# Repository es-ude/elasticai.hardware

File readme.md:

# elasticAI.hardware
This repo contains the hardware design files for different generations of the Elastic Node Hardware (ENv). 
This hardware is used for deploying deep learning architectures on embedded hardware and in applications.

## ENv6 - Elastic Node v6
Still in development. See further detailed information in their specific [docu file](v6/readme.md).

## ENv5 - Elastic Node v5
Actual version. See further detailed information in [docu](v5/readme.md).

## ENv4 - Elastic Node v4
Designs are deprecated and not longer used.

## ENv3 - Elastic Node v3
Designs are deprecated and not longer used.

## ENv2 - Elastic Node v2
Designs are deprecated and not longer used.

## ENv1 - Elastic Node v1
Designs are deprecated and not longer used.

## power - Elastic Power Modules
Designs are the actual version. See further detailed information in [docu](power/readme.md).

## measurement - Measurement Equipment for R&S MXO4
This two designs can be used for performing Frequency Response Analysis using the R&S MXO4 oscilloscope in which the Device-Under-Test (DUT) needs an input offset.
State: Active used

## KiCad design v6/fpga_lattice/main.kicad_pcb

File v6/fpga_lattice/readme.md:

# ENv6 FPGA Board: Lattice iCE40UP5K

FPGA board (shield, rev 1.0, 4-layer PCB) for the ENv6 base board. FPGA board ID: **1** (R2 = 1 kΩ to GND on `FPGA_DETECT`, see the [auto-identification](../readme.md#auto-identification-of-connected-boards)).

## Contents

- Lattice iCE40UP5K-SG48 (U1)
- W25Q16JVUX quad-SPI flash (U2), shared with the MCU via the SPI1/QSPI lines of the connector
- Si5351A clock generator (J1) with 25 MHz crystal (Y1): controlled by the MCU via I2C, output enable `FPGA_OSC_EN`; one output drives the FPGA global clock input (`FPGA_SYS_CLK`, test point TP1), a second output is available at test point TP2
- Status LED (D1, R1 = 750 Ω) on an FPGA IO (`IOT_36B`)
- ID resistor R2 (1 kΩ) on `FPGA_DETECT`
- Pull-ups (R3 … R7, 10 kΩ to `VDD`) on the flash lines `WP`, `HOLD`, `CS` and on `FPGA_PR_~{RST}`, `FPGA_PR_DONE`

## Power Supply

| Rail   | Pins      | Net    | Use                                                  |
|--------|-----------|--------|------------------------------------------------------|
| `PSU1` | C3 … C8   | `+1V2` | iCE40 core (`VCC`) and PLL (`VCCPLL`)                |
| `PSU4` | C19 … C24 | `VDD`  | I/O banks, `VPP_2V5`, flash, Si5351A, pull-ups       |

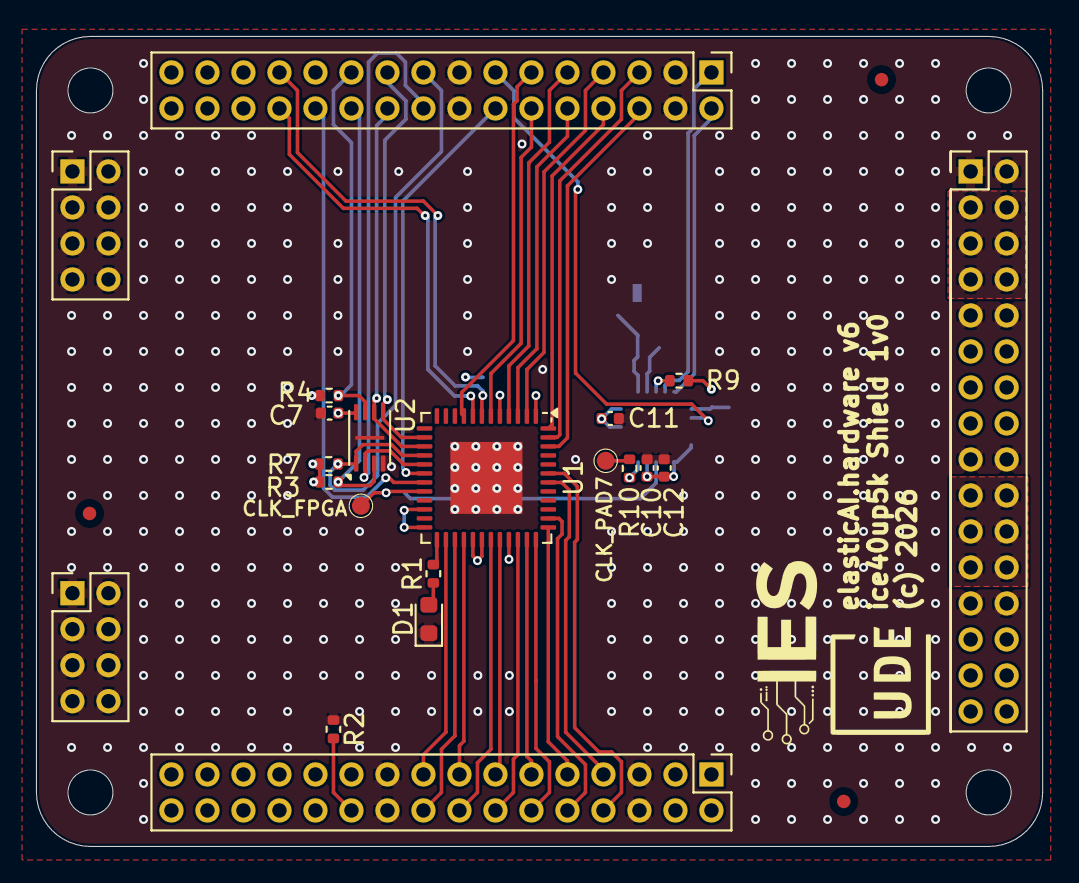
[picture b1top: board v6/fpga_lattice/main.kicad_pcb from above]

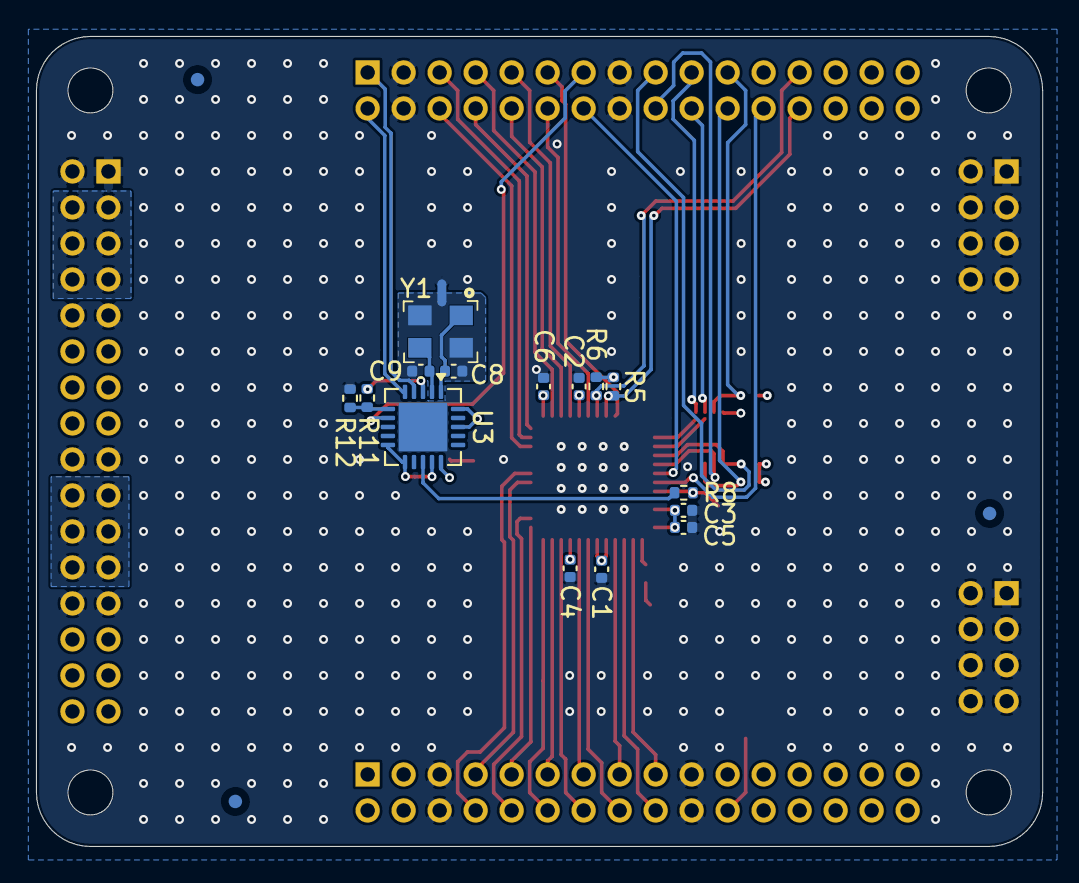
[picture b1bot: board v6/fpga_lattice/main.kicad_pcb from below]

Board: 4 copper layers, 55.9 x 45.0 mm, 39 parts (19 on the bottom side), 48 nets.

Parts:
B1: ExtensionBoard_ENv6
C1, C2, C3, C4, C5, C6, C7, C10, C11, C12: 1u; C_0402_1005Metric
C8, C9: 12p; C_0402_1005Metric
D1: LED_0603; LED_0603_1608Metric
FID1, FID2, FID3, FID4, FID5, FID6: Fiducial; Fiducial_0.75mm_Mask1.5mm
NT1: NetTie_2; NetTie-2_SMD_Pad0.5mm
R1: 750R; R_0402_1005Metric
R2: 1k; R_0402_1005Metric
R3, R4, R5, R6, R7: 10k; R_0402_1005Metric
R8, R9, R10, R11, R12: 27R; R_0402_1005Metric
TP1: CLK_FPGA; TestPoint_Pad_D1.0mm
TP2: CLK_PAD7; TestPoint_Pad_D1.0mm
U1: ICE40UP5K-SG48ITR50; QFN-48-1EP_7x7mm_P0.5mm_EP5.15x5.15mm
U2: W25Q16JVUX; USON-8-1EP_3x2mm_P0.5mm_EP0.2x1.6mm
U3: Si5351A-B-GM; QFN-20-1EP_4x4mm_P0.5mm_EP2.7x2.7mm
Y1: KX7-25M; KX-7

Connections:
+1V2: B1.C3, B1.C4, B1.C5, B1.C6, B1.C7, B1.C8, C1.2, C2.2, U1.5 (VCC), U1.29 (VCCPLL), U1.30 (VCC)
/FLASH_~CS: B1.A17, R7.2, U1.16 (IOB_35B_SPI_SS), U2.1 (~CS)
/FPGA_FLASH_SI: B1.A19, U1.14 (IOB_32A_SPI_SO), U2.5 (SI/IO0)
/FPGA_FLASH_SK: B1.A20, U1.15 (IOB_34A_SPI_SCK), U2.6 (SCK)
/FPGA_FLASH_SO: B1.A18, U1.17 (IOB_33B_SPI_SI), U2.2 (SO/IO1)
/FPGA_FLASH_~HD: B1.A21, R4.2, U2.7 (~HOLD/IO3)
/FPGA_FLASH_~WP: B1.A22, R3.2, U2.3 (~WP/IO2)
/FPGA_IO_0: B1.A5, U1.47 (IOB_2A)
/FPGA_IO_1: B1.A6, U1.46 (IOB_0A)
/FPGA_IO_2: B1.A7, U1.2 (IOB_6A)
/FPGA_IO_3: B1.A8, U1.48 (IOB_4A)
/FPGA_IO_4: B1.A9, U1.4 (IOB_8A)
/FPGA_IO_5: B1.A10, U1.3 (IOB_9B)
/FPGA_IO_6: B1.A11, U1.9 (IOB_16A)
/FPGA_IO_7: B1.A12, U1.6 (IOB_13B)
/FPGA_IO_A_0: B1.B18, U1.27 (IOT_38B)
/FPGA_IO_A_1: B1.B17, U1.26 (IOT_39A)
/FPGA_IO_A_2: B1.B16, U1.31 (IOT_42B)
/FPGA_IO_A_3: B1.B15, U1.28 (IOT_41A)
/FPGA_IO_A_4: B1.B14, U1.34 (IOT_44B)
/FPGA_IO_A_5: B1.B13, U1.32 (IOT_43A)
/FPGA_IO_A_6: B1.B12, U1.36 (IOT_48B)
/FPGA_IO_A_7: B1.B11, U1.35 (IOT_46B_G0)
/FPGA_IO_A_8: B1.B10, U1.38 (IOT_50B)
/FPGA_IO_A_9: B1.B9, U1.37 (IOT_45A_G1)
/FPGA_IO_A_10: B1.B8, U1.43 (IOT_49A)
/FPGA_IO_A_11: B1.B7, U1.42 (IOT_51A)
/FPGA_OSC_EN: B1.A13, U3.7 (OEB)
/FPGA_PR_DONE: B1.A25, R6.2, U1.7 (CDONE)
/FPGA_PR_~RST: B1.A26, R5.2, U1.8 (~CRESET_B)
/FPGA_SYS_CLK: R8.2, TP1.1 (1_1), U1.20 (IOB_25B_G3)
/FPGA_USR_~RST: B1.A24, U1.19 (IOB_29B)
/FPGA_~CS: B1.A14, U1.18 (IOB_31B)
/GND_QRZ: C8.2, C9.2, NT1.2, Y1.2 (SH), Y1.4 (SH)
/I2C_SCL: B1.A1, U3.4 (SCL)
/I2C_SDA: B1.A2, U3.5 (SDA)
GND: B1.A3, B1.A4, B1.A15, B1.A16, B1.B5, B1.B6, B1.B19, B1.B20, B1.C1, B1.C2, B1.C9, B1.C10, B1.C17, B1.C18, B1.C25, B1.C26, B1.D1, B1.D2, B1.D3, B1.D4, B1.D5, B1.D6, B1.D7, B1.D8, B1.E1, B1.E2, B1.E3, B1.E4, B1.E5, B1.E6, B1.E7, B1.E8, C1.1, C2.1, C3.2, C4.2, C5.2, C6.2, C7.2, C10.2, C11.2, C12.2, D1.1 (K), NT1.1, R2.1, R12.2, U1.49 (GND), U2.4 (VSS), U2.9 (VSS), U3.21 (GND)
unnamed: B1.B22, R2.2
unnamed: D1.2 (A), R1.1
unnamed: R10.2, TP2.1 (1_1)
unnamed: R1.2, U1.25 (IOT_36B)
unnamed: R9.1, U3.3 (A0)
unnamed: R8.1, U3.13 (CLK0)
unnamed: R10.1, U3.15 (CLK7)
unnamed: R11.1, R12.1, U3.6 (SSEN)
unnamed: C8.1, U3.1 (XA), Y1.1
unnamed: C9.1, U3.2 (XB), Y1.3
VDD: B1.C19, B1.C20, B1.C21, B1.C22, B1.C23, B1.C24, C3.1, C4.1, C5.1, C6.1, C7.1, C10.1, C11.1, C12.1, R3.1, R4.1, R5.1, R6.1, R7.1, R9.2, R11.2, U1.1 (VCCIO_2), U1.22 (SPI_VCCIO_1), U1.24 (VPP_2V5), U1.33 (VCCIO_0), U2.8 (VCC), U3.10 (VDDOB), U3.11 (VDDOA), U3.14 (VDDOD), U3.18 (VDDOC), U3.20 (VDD)

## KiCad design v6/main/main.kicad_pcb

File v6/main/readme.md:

# ENv6 Base Board

Base board of the ENv6 stack. It carries the MCU, wireless, USB, power management and current sensing, and provides the connector to the swappable FPGA board and the optional application board (see the [top-level readme](../readme.md) for the connector description and the auto-identification scheme).

## Contents

| Block (KiCad sheet)                   | Main parts                                                                                                                                                                                                                                                                                                                                      |
|---------------------------------------|-------------------------------------------------------------------------------------------------------------------------------------------------------------------------------------------------------------------------------------------------------------------------------------------------------------------------------------------------|
| MCU (`MCU.kicad_sch`)                 | RP2354B (U402), 12 MHz crystal, W25Q16 QSPI flash (U401, optional with internal-flash variant), Raspberry Pi radio module (U403) for WLAN, WS2812B status LED (D401), BOOTSEL / RESET / one user button, SWD debug connector (J401), 1×4 header for an external FPGA JTAG probe (J402), board detection (two 10 kΩ pull-ups R401/R402 + 1 µF)   |
| Power (`Power.kicad_sch`)             | USB-C (J302), Li-ion battery connector (J_BATT301), BQ25188 charger (U301), LP873300 programmable multi-output supply (IC301, four rails PSU1 … PSU4), TLV73333 3.3 V LDO (U302)                                                                                                                                                                |
| Peripherals (`Peripherals.kicad_sch`) | PAC1954 4-channel current/power monitor (U201, 1 Ω shunts), microSD slot (J201, SPI0), 2×2 headers to route the four supply rails through an external Nordic PPK2                                                                                                                                                                               |
| Connector (`connector.kicad_sch`)     | ENv6 base-board connector (MCU/FPGA header, application header, power header, GND headers)                                                                                                                                                                                                                                                      |

## Interfaces

Pin numbers refer to the connector `B401`; the complete pin tables are in the [top-level readme](../readme.md#connector-of-the-base-board).

| Interface                                            | MCU pins                                                           | Connector pins                    |
|------------------------------------------------------|--------------------------------------------------------------------|-----------------------------------|
| I2C0 (also PAC1954)                                  | GP0 (SDA), GP1 (SCL)                                               | A2, A1                            |
| SPI1 to the FPGA board                               | GP12 (RX), GP13 (CS), GP14 (SCK), GP15 (TX)                        | A18, A17, A20, A19                |
| Quad-SPI data lines                                  | GP16 (IO2), GP17 (IO3)                                             | A22, A21                          |
| JTAG                                                 | GP26 (TCK), GP27 (TDO), GP28 (TDI), GP30 (TMS)                     | A30, A29, A32, A31                |
| Configuration lines `FPGA_CFG_1 … 4`                 | GP19 … GP22                                                        | A26, A25, A28, A27                |
| `MCU-FPGA_CS`, `MCU-FPGA_EN_OSC`, `MCU-FPGA_USR-RST` | GP10, GP11, GP18                                                   | A14, A13, A24                     |
| Unused GPIOs                                         | GP2 … GP9                                                          | A6, A5, A8, A7, A10, A9, A12, A11 |
| Application GPIOs / ADC                              | GP33 … GP35, GP40 … GP45 (ADC0 … ADC5)                             | B31 … B29, B28 … B23              |
| Board detection (ADC)                                | GP46 (`FPGA_DETECT`), GP47 (`APP_DETECT`)                          | B22, B21                          |
| microSD                                              | SPI0: GP36 (RX), GP37 (CS), GP38 (SCK), GP39 (TX)                  | –                                 |
| Radio module                                         | GP23 (`WL_EN`), GP24 (`WL_DATA`), GP25 (`WL_CS`), GP29 (`WL_SCLK`) | –                                 |
| Status LED / button                                  | GP31 (WS2812B), GP32 (user button)                                 | –                                 |

Supply: `VDD_MCU` (3.3 V from the TLV73333) feeds the MCU, `AVDD_ADC` and the detection pull-ups (R401, R402); it is also available on A23 and B32. `VSYS` is on B1 … B4, the four programmable rails `PSU1 … PSU4` on C3 … C32.

BOM: [iBOM](bom/ibom.html)

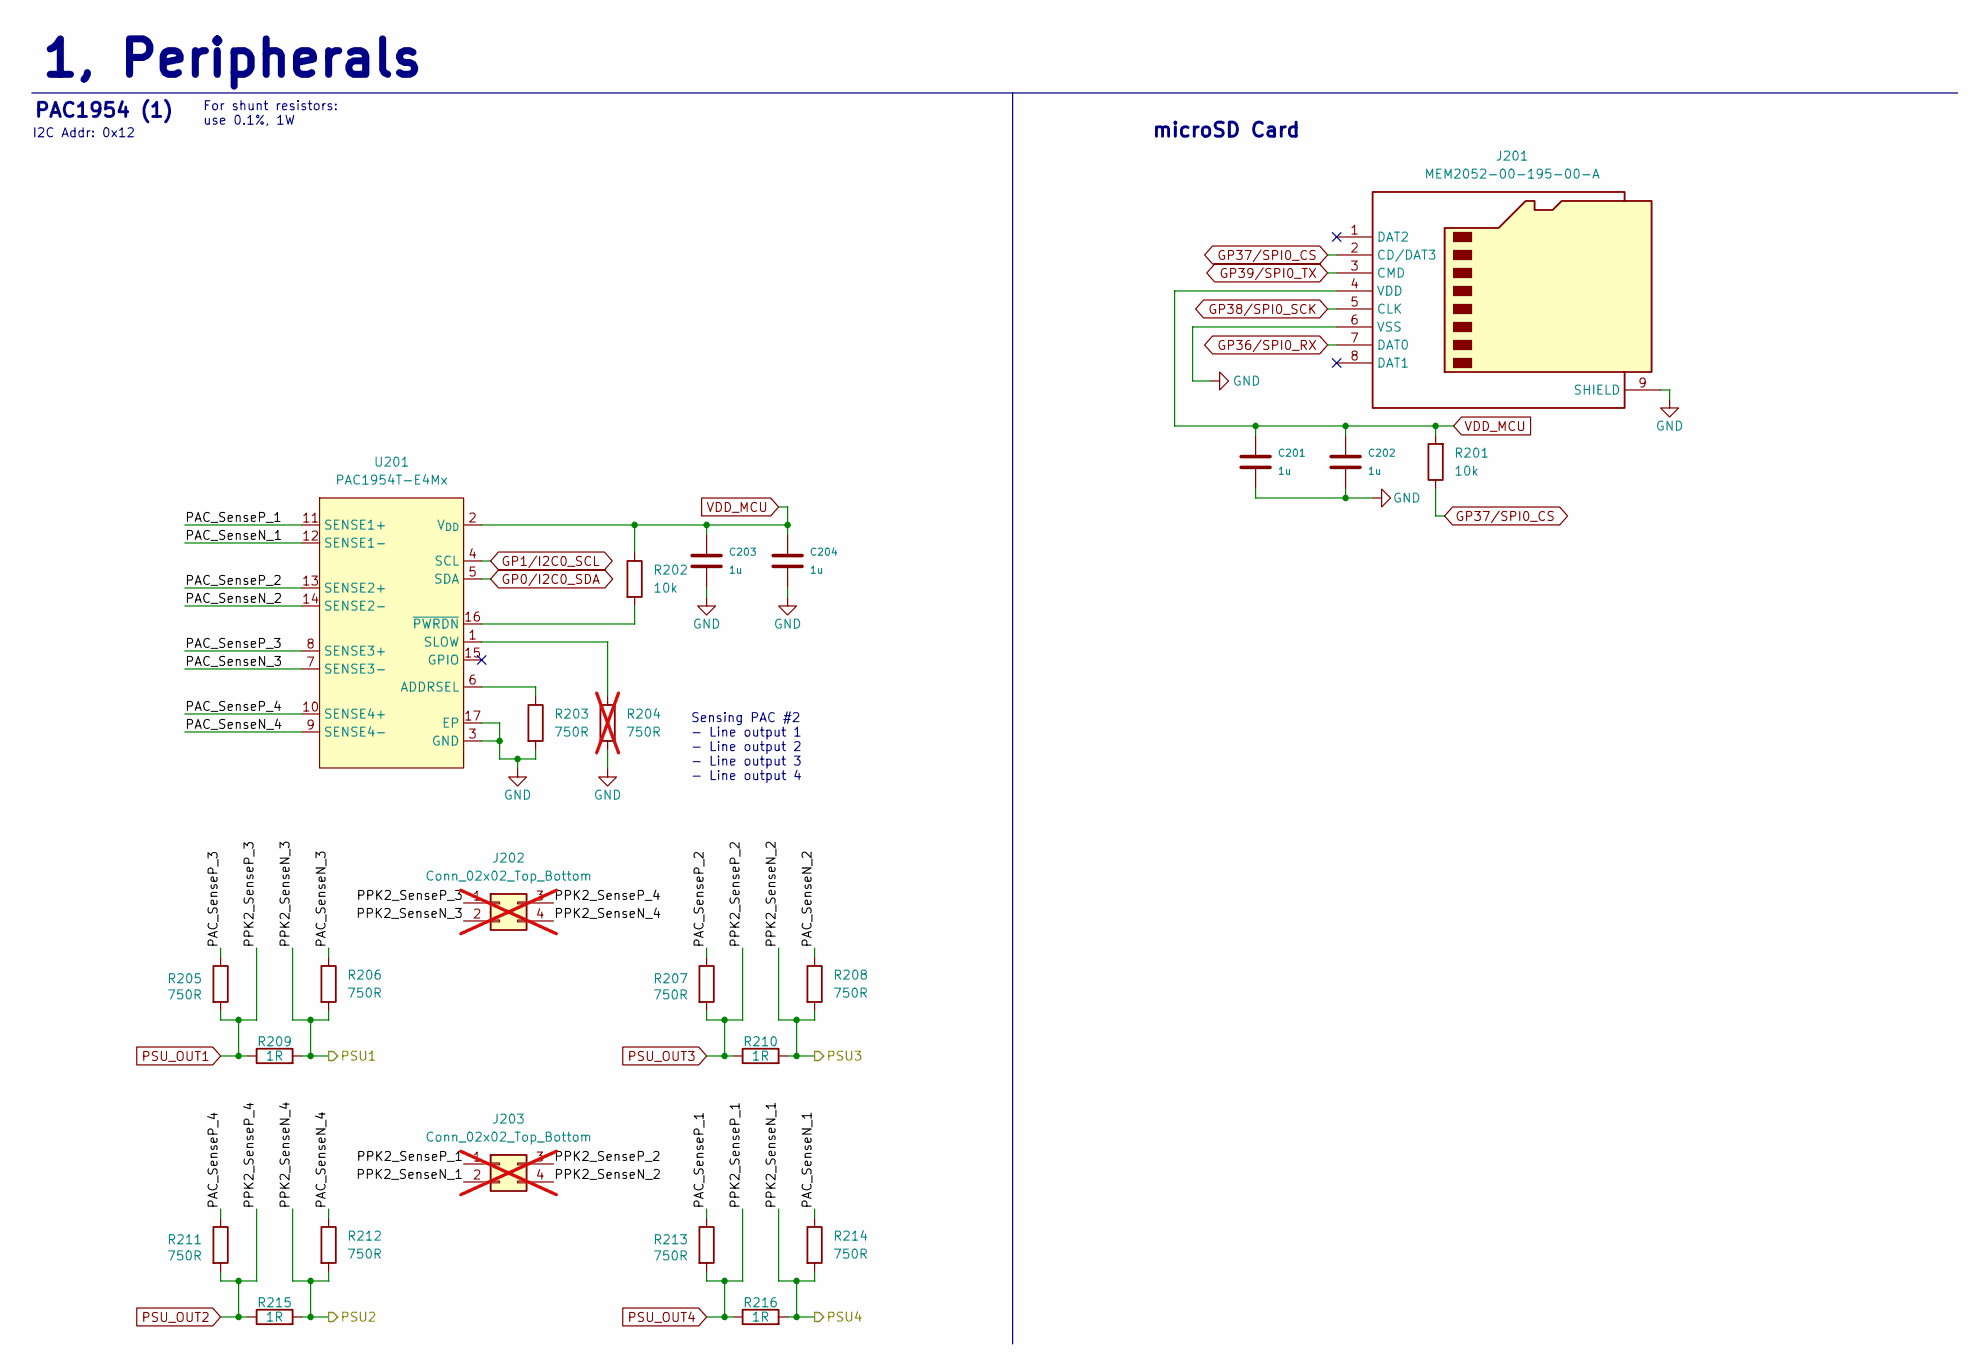
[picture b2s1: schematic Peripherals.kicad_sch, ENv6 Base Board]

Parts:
C201, C202, C203, C204: 1u; C_0402_1005Metric
J201: MEM2052-00-195-00-A; MEM20520019500A; Mouser Part Number 640-MEM20520019500A
J202, J203: Conn_02x02_Top_Bottom; PinHeader_2x02_P2.00mm_Vertical; not fitted
R201, R202: 10k; R_0402_1005Metric
R203, R205, R206, R207, R208, R211, R212, R213, R214: 750R; R_0402_1005Metric
R204: 750R; R_0402_1005Metric; not fitted
R209, R210, R215, R216: 1R; R_0603_1608Metric
U201: PAC1954T-E4Mx; VQFN-16-1EP_3x3mm_P0.5mm_EP1.1x1.1mm

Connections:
/Peripherals/PAC_SenseN_1: R214.1, U201.12 (SENSE1-)
/Peripherals/PAC_SenseN_2: R208.1, U201.14 (SENSE2-)
/Peripherals/PAC_SenseN_3: R206.1, U201.7 (SENSE3-)
/Peripherals/PAC_SenseN_4: R212.1, U201.9 (SENSE4-)
/Peripherals/PAC_SenseP_1: R213.1, U201.11 (SENSE1+)
/Peripherals/PAC_SenseP_2: R207.1, U201.13 (SENSE2+)
/Peripherals/PAC_SenseP_3: R205.1, U201.8 (SENSE3+)
/Peripherals/PAC_SenseP_4: R211.1, U201.10 (SENSE4+)
/V1: J202.2, R206.2, R209.2; also elsewhere on the board
/V2: J202.4, R212.2, R215.2; also elsewhere on the board
/V3: J203.4, R208.2, R210.2; also elsewhere on the board
/V4: J203.2, R214.2, R216.2; also elsewhere on the board
GND: C201.1, C202.1, C203.1, C204.1, J201.6 (VSS), J201.9 (SHIELD), J201.G1 (GND_1), J201.G2 (GND_2), J201.G3 (GND_3), J201.G4 (GND_4), R203.2, R204.2, U201.3 (GND), U201.17 (EP); also elsewhere on the board
GP0/I2C0_SDA: U201.5 (SDA); also elsewhere on the board
GP1/I2C0_SCL: U201.4 (SCL); also elsewhere on the board
GP36/SPI0_RX: J201.7 (DAT0); also elsewhere on the board
GP37/SPI0_CS: J201.2 (CD/DAT3), R201.1; also elsewhere on the board
GP38/SPI0_SCK: J201.5 (CLK); also elsewhere on the board
GP39/SPI0_TX: J201.3 (CMD); also elsewhere on the board
unnamed: R203.1, U201.6 (ADDRSEL)
unnamed: R204.1, U201.1 (SLOW)
unnamed: R202.2, U201.16 (~PWRDN)
PSU_OUT1: J202.1, R205.2, R209.1; also elsewhere on the board
PSU_OUT2: J202.3, R211.2, R215.1; also elsewhere on the board
PSU_OUT3: J203.3, R207.2, R210.1; also elsewhere on the board
PSU_OUT4: J203.1, R213.2, R216.1; also elsewhere on the board
VDD_MCU: C201.2, C202.2, C203.2, C204.2, J201.4 (VDD), R201.2, R202.1, U201.2 (V_{DD}); also elsewhere on the board

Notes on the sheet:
1, Peripherals
PAC1954 (1)
microSD Card
For shunt resistors: use 0.1%, 1W
I2C Addr: 0x12
Sensing PAC #2 - Line output 1 - Line output 2 - Line output 3 - Line output 4

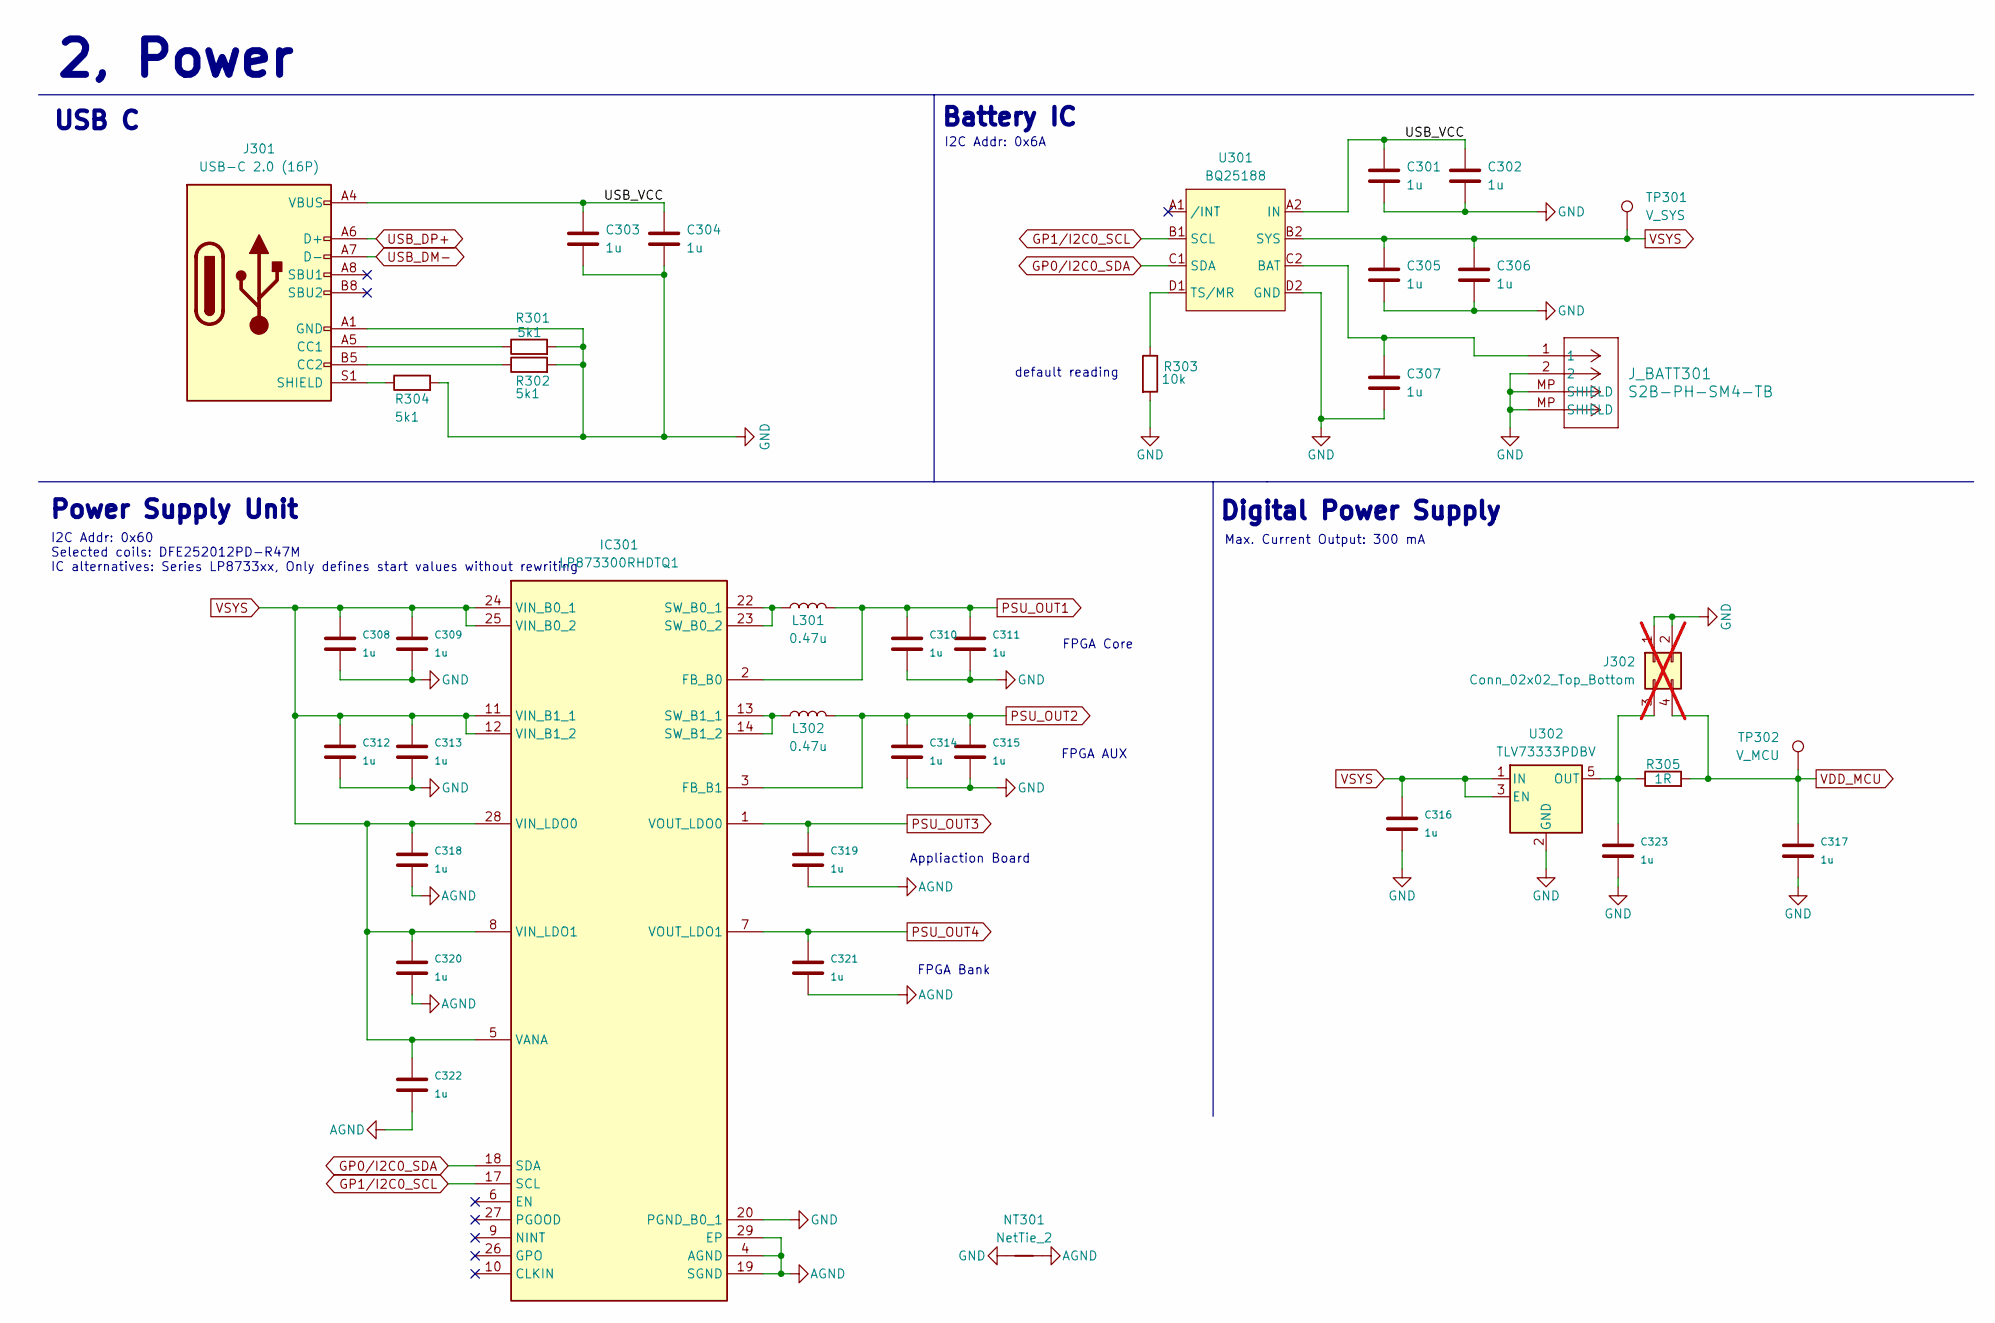
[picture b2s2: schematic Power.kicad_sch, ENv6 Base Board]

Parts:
C301, C302, C303, C304, C305, C306, C307, C308, C309, C310, C311, C312, C313, C314, C315, C316, C317, C318, C319, C320, C321, C322, C323: 1u; C_0402_1005Metric
IC301: LP873300RHDTQ1; QFN50P500X500X100-29N-D; Mouser Part Number 595-LP873300RHDTQ1
J301: USB-C 2.0 (16P); USB_C_Receptacle_16P; MPN 629722000214
J302: Conn_02x02_Top_Bottom; PinHeader_2x02_P2.00mm_Vertical; not fitted
J_BATT301: S2B-PH-SM4-TB; JST_PH_S2B-PH-SM4-TB_1x02-1MP_P2.00mm_Horizontal
L301, L302: 0.47u; L_1008_2520Metric
NT301: NetTie_2; NetTie-2_SMD_Pad0.5mm
R301, R302, R304: 5k1; R_0402_1005Metric
R303: 10k; R_0402_1005Metric
R305: 1R; R_0603_1608Metric
TP301: V_SYS; TestPoint_Pad_D1.0mm
TP302: V_MCU; TestPoint_Pad_D1.0mm
U301: BQ25188; Texas_DSBGA-8_0.9x1.9mm_Layout2x4_P0.5mm
U302: TLV73333PDBV; SOT-23-5

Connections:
/Power/USB_VCC: C301.1, C302.1, C303.1, C304.1, J301.A4 (VBUS), J301.A9 (VBUS), J301.B4 (VBUS), J301.B9 (VBUS), U301.A2 (IN)
AGND: C318.1, C319.1, C320.1, C321.1, C322.1, IC301.4 (AGND), IC301.19 (SGND), IC301.29 (EP), NT301.2
GND: C301.2, C302.2, C303.2, C304.2, C305.2, C306.2, C307.2, C308.1, C309.1, C310.1, C311.1, C312.1, C313.1, C314.1, C315.1, C316.1, C317.1, C323.1, IC301.15 (PGND_B1_1), IC301.16 (PGND_B1_2), IC301.20 (PGND_B0_1), IC301.21 (PGND_B0_2), J301.A1 (GND), J301.A12 (GND), J301.B1 (GND), J301.B12 (GND), J302.1, J302.2, J_BATT301.2, J_BATT301.MP (SHIELD), NT301.1, R301.2, R302.2, R303.2, R304.2, U301.D2 (GND), U302.2 (GND); also elsewhere on the board
GP0/I2C0_SDA: IC301.18 (SDA), U301.C1 (SDA); also elsewhere on the board
GP1/I2C0_SCL: IC301.17 (SCL), U301.B1 (SCL); also elsewhere on the board
unnamed: IC301.22 (SW_B0_1), IC301.23 (SW_B0_2), L301.1
unnamed: IC301.13 (SW_B1_1), IC301.14 (SW_B1_2), L302.1
unnamed: J301.A5 (CC1), R301.1
unnamed: J301.B5 (CC2), R302.1
unnamed: J301.S1 (SHIELD), R304.1
unnamed: C323.2, J302.3, R305.1, U302.5 (OUT)
unnamed: C307.1, J_BATT301.1, U301.C2 (BAT)
unnamed: R303.1, U301.D1 (TS/MR)
PSU_OUT1: C310.2, C311.2, IC301.2 (FB_B0), L301.2; also elsewhere on the board
PSU_OUT2: C314.2, C315.2, IC301.3 (FB_B1), L302.2; also elsewhere on the board
PSU_OUT3: C319.2, IC301.1 (VOUT_LDO0); also elsewhere on the board
PSU_OUT4: C321.2, IC301.7 (VOUT_LDO1); also elsewhere on the board
USB_DM-: J301.A7 (D-), J301.B7 (D-); also elsewhere on the board
USB_DP+: J301.A6 (D+), J301.B6 (D+); also elsewhere on the board
VDD_MCU: C317.2, J302.4, R305.2, TP302.1 (1_1); also elsewhere on the board
VSYS: C305.1, C306.1, C308.2, C309.2, C312.2, C313.2, C316.2, C318.2, C320.2, C322.2, IC301.5 (VANA), IC301.8 (VIN_LDO1), IC301.11 (VIN_B1_1), IC301.12 (VIN_B1_2), IC301.24 (VIN_B0_1), IC301.25 (VIN_B0_2), IC301.28 (VIN_LDO0), TP301.1 (1_1), U301.B2 (SYS), U302.1 (IN), U302.3 (EN); also elsewhere on the board

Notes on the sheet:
Battery IC
FPGA Bank
I2C Addr: 0x6A
default reading
Max. Current Output: 300 mA
USB C
2, Power
FPGA Core
Power Supply Unit
FPGA AUX
I2C Addr: 0x60 Selected coils: DFE252012PD-R47M IC alternatives: Series LP8733xx, Only defines start values without rewriting
Digital Power Supply
Appliaction Board

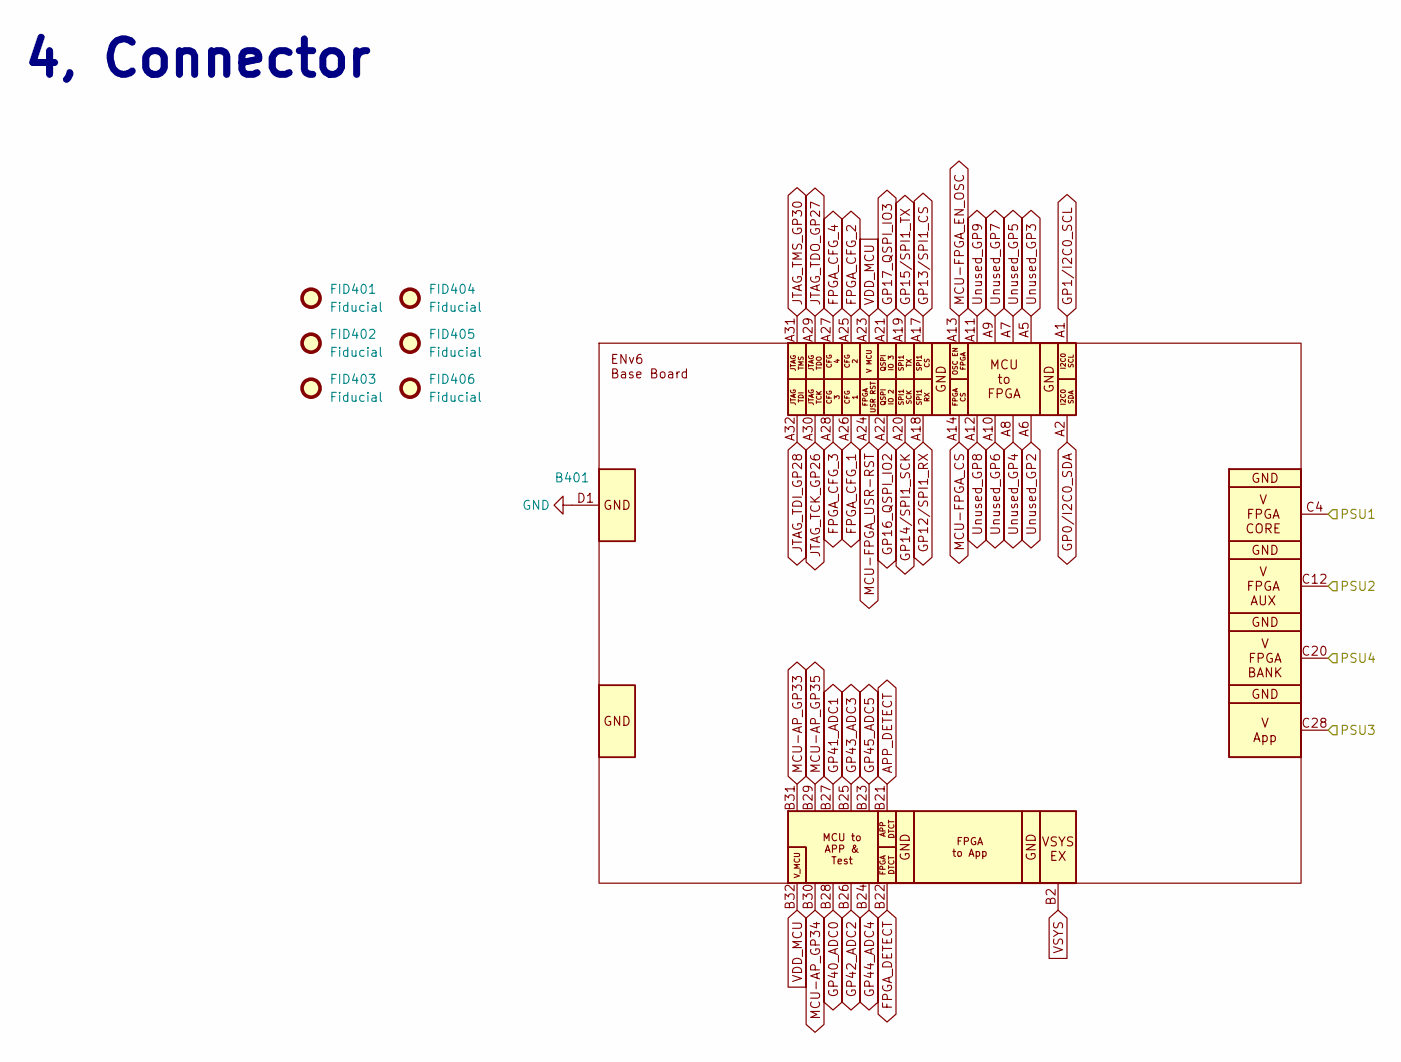
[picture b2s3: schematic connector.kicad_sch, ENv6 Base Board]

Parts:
B401: BaseBoard_ENv6
FID401, FID402, FID403, FID404, FID405, FID406: Fiducial; Fiducial_0.75mm_Mask1.5mm

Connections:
/V1: B401.C3, B401.C4, B401.C5, B401.C6, B401.C7, B401.C8; also elsewhere on the board
/V2: B401.C11, B401.C12, B401.C13, B401.C14, B401.C15, B401.C16; also elsewhere on the board
/V3: B401.C27, B401.C28, B401.C29, B401.C30, B401.C31, B401.C32; also elsewhere on the board
/V4: B401.C19, B401.C20, B401.C21, B401.C22, B401.C23, B401.C24; also elsewhere on the board
APP_DETECT: B401.B21; also elsewhere on the board
FPGA_CFG_1: B401.A26; also elsewhere on the board
FPGA_CFG_2: B401.A25; also elsewhere on the board
FPGA_CFG_3: B401.A28; also elsewhere on the board
FPGA_CFG_4: B401.A27; also elsewhere on the board
FPGA_DETECT: B401.B22; also elsewhere on the board
GND: B401.A3, B401.A4, B401.A15, B401.A16, B401.B5, B401.B6, B401.B19, B401.B20, B401.C1, B401.C2, B401.C9, B401.C10, B401.C17, B401.C18, B401.C25, B401.C26, B401.D1, B401.D2, B401.D3, B401.D4, B401.D5, B401.D6, B401.D7, B401.D8, B401.E1, B401.E2, B401.E3, B401.E4, B401.E5, B401.E6, B401.E7, B401.E8; also elsewhere on the board
GP0/I2C0_SDA: B401.A2; also elsewhere on the board
GP1/I2C0_SCL: B401.A1; also elsewhere on the board
GP12/SPI1_RX: B401.A18; also elsewhere on the board
GP13/SPI1_CS: B401.A17; also elsewhere on the board
GP14/SPI1_SCK: B401.A20; also elsewhere on the board
GP15/SPI1_TX: B401.A19; also elsewhere on the board
GP16_QSPI_IO2: B401.A22; also elsewhere on the board
GP17_QSPI_IO3: B401.A21; also elsewhere on the board
GP40_ADC0: B401.B28; also elsewhere on the board
GP41_ADC1: B401.B27; also elsewhere on the board
GP42_ADC2: B401.B26; also elsewhere on the board
GP43_ADC3: B401.B25; also elsewhere on the board
GP44_ADC4: B401.B24; also elsewhere on the board
GP45_ADC5: B401.B23; also elsewhere on the board
JTAG_TCK_GP26: B401.A30; also elsewhere on the board
JTAG_TDI_GP28: B401.A32; also elsewhere on the board
JTAG_TDO_GP27: B401.A29; also elsewhere on the board
JTAG_TMS_GP30: B401.A31; also elsewhere on the board
MCU-AP_GP33: B401.B31; also elsewhere on the board
MCU-AP_GP34: B401.B30; also elsewhere on the board
MCU-AP_GP35: B401.B29; also elsewhere on the board
MCU-FPGA_CS: B401.A14; also elsewhere on the board
MCU-FPGA_EN_OSC: B401.A13; also elsewhere on the board
MCU-FPGA_USR-RST: B401.A24; also elsewhere on the board
Unused_GP2: B401.A6; also elsewhere on the board
Unused_GP3: B401.A5; also elsewhere on the board
Unused_GP4: B401.A8; also elsewhere on the board
Unused_GP5: B401.A7; also elsewhere on the board
Unused_GP6: B401.A10; also elsewhere on the board
Unused_GP7: B401.A9; also elsewhere on the board
Unused_GP8: B401.A12; also elsewhere on the board
Unused_GP9: B401.A11; also elsewhere on the board
VDD_MCU: B401.A23, B401.B32; also elsewhere on the board
VSYS: B401.B1, B401.B2, B401.B3, B401.B4; also elsewhere on the board

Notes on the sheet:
4, Connector

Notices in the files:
power/0_dcdc_max/power.kicad_pcb:
1v0 (c) 2026
v6/fpga_gatemate/main.kicad_pcb:
(c) 2026
parts and their libraries:
License: Apache-2.0
